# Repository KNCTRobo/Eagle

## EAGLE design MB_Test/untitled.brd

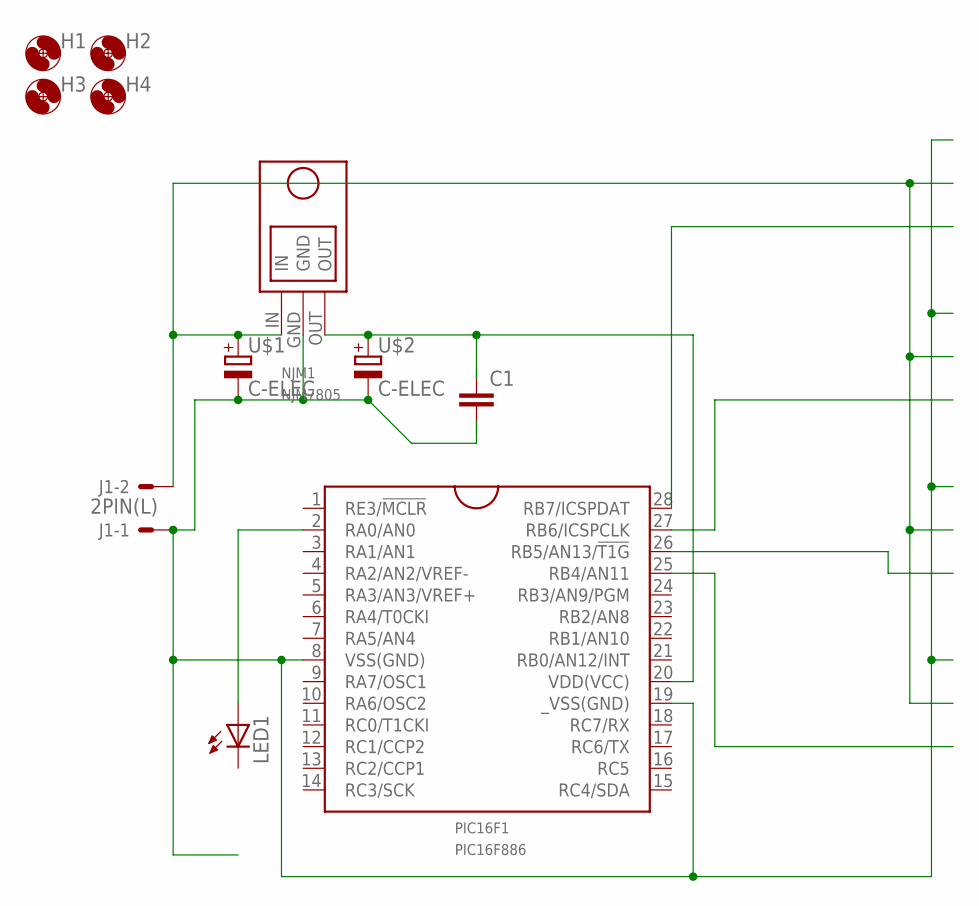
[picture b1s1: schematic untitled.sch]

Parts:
C1: C-; C-2.54
H1, H2, H3, H4: HOLE3.3M3BOLT; HOLE3.3
J1: 2PIN(L); 2PL
LED1: LED; LED5MM
NJM1: NJM7805
PIC16F1: PIC16F886; DIL28-3
U$1, U$2: C-ELEC; C-6MM

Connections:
unnamed: J1.1, NJM1.GND, PIC16F1.8 (VSS(GND)), PIC16F1.19 (_VSS(GND)), U$1.-, U$2.-
unnamed: J1.2, NJM1.IN, U$1.+
unnamed: NJM1.OUT, PIC16F1.20 (VDD(VCC)), U$2.+
unnamed: LED1.A, PIC16F1.2 (RA0/AN0)

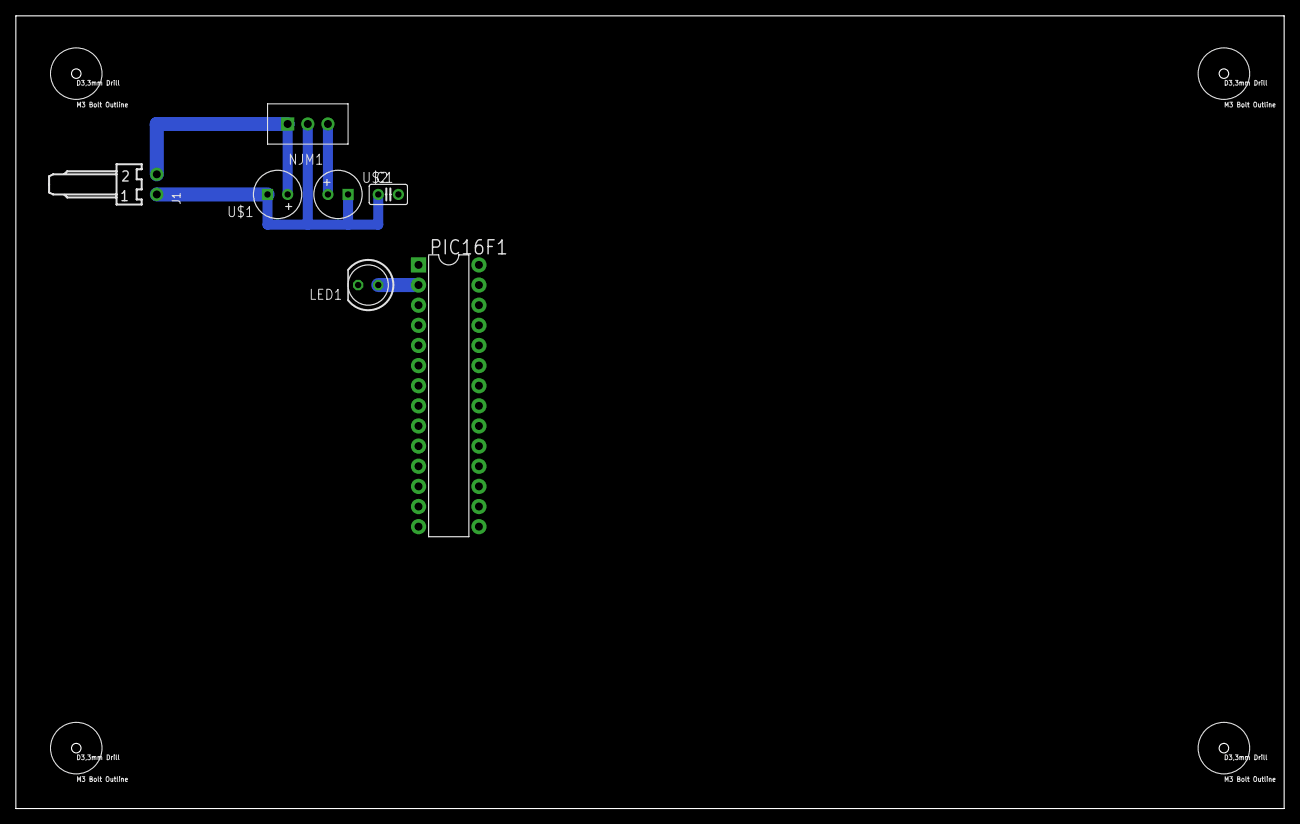
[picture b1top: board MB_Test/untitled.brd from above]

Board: 2 copper layers, 160.0 x 100.0 mm, 11 parts (0 on the bottom side), 4 nets.

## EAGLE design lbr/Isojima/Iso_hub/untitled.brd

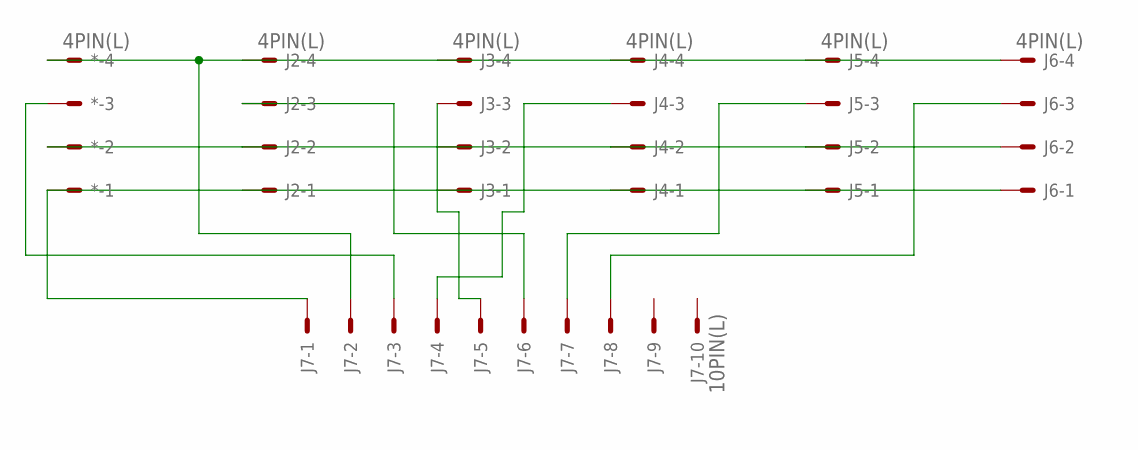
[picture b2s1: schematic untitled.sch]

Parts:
*: 4PIN(L); 4PL
J2, J3, J4, J5, J6: 4PIN(L); 4PL
J7: 10PIN(L); 10PL

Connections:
unnamed: *.4, J2.4, J3.4, J4.4, J5.4, J6.4, J7.2
unnamed: *.1, J2.1, J3.1, J4.1, J5.1, J6.1, J7.1
unnamed: *.2, J2.2, J3.2, J4.2, J5.2, J6.2
unnamed: *.3, J7.3
unnamed: J2.3, J7.6
unnamed: J3.3, J7.5
unnamed: J4.3, J7.4
unnamed: J5.3, J7.7
unnamed: J6.3, J7.8

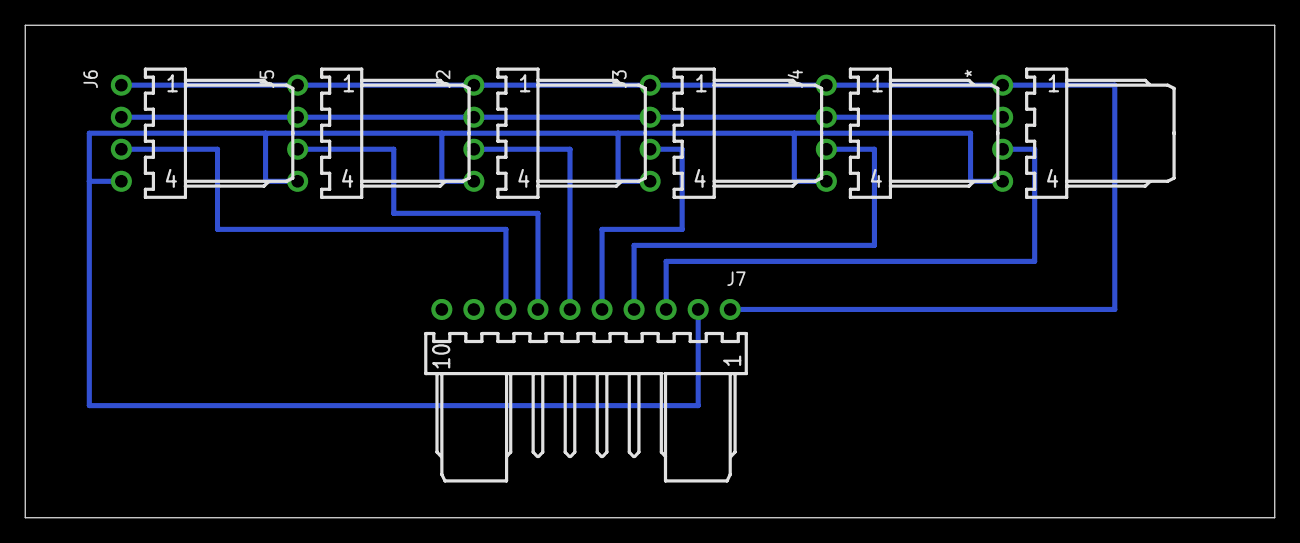
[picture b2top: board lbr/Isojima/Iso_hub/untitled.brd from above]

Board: 2 copper layers, 99.0 x 39.0 mm, 7 parts (0 on the bottom side), 9 nets.

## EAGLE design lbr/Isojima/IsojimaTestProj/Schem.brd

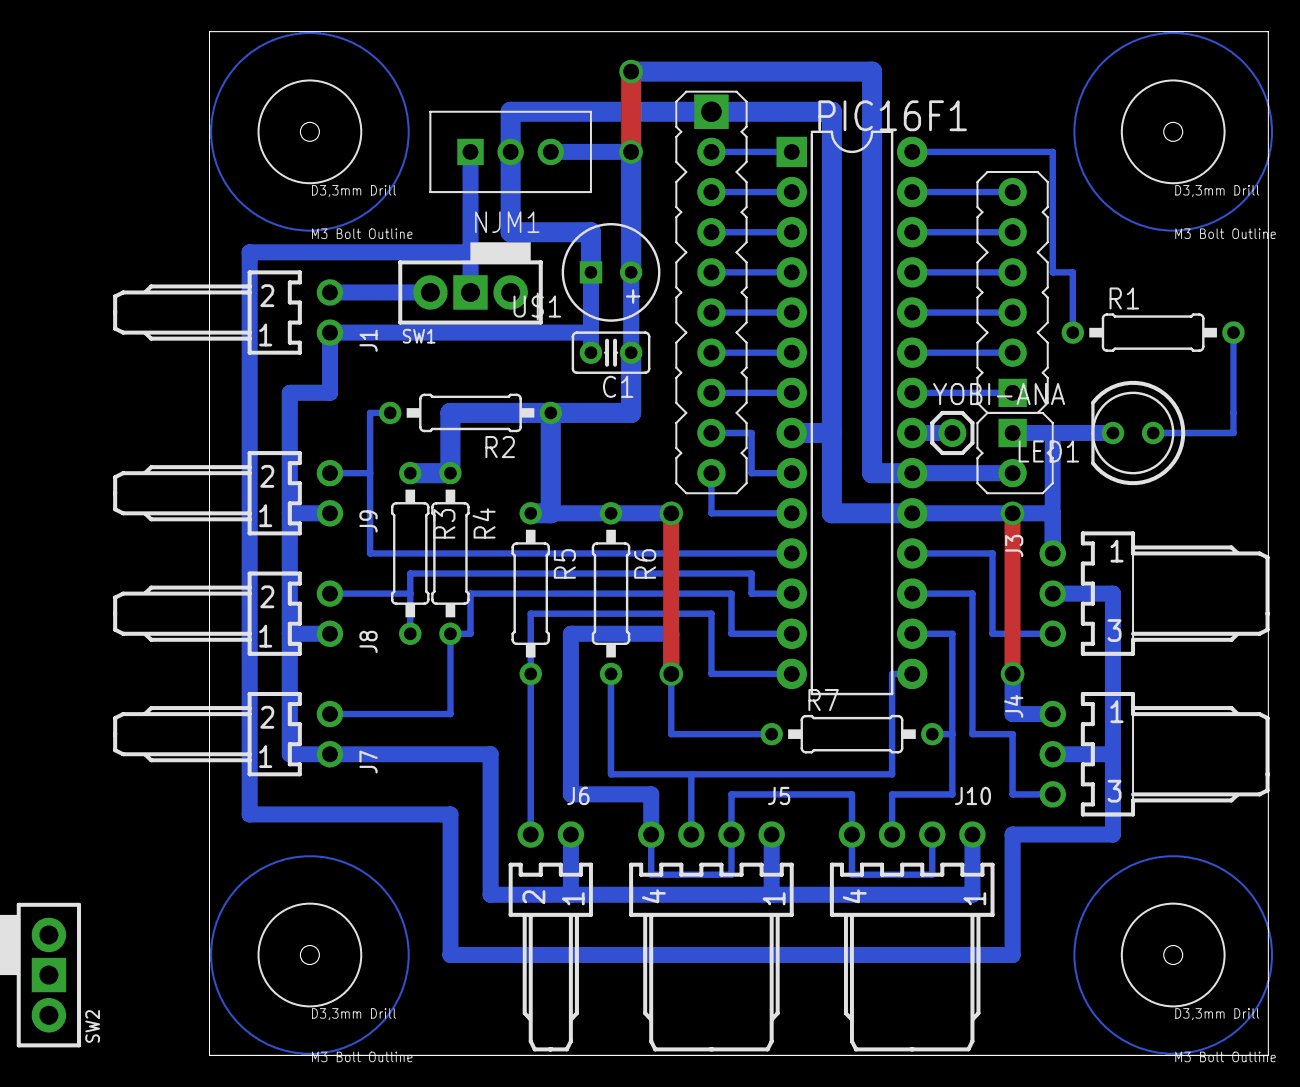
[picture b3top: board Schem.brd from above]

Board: 2 copper layers, 67.0 x 64.8 mm, 31 parts (0 on the bottom side), 30 nets.

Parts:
C1: C-2.54
H1, H2, H3, H4: HOLE3.3M3BOLT; HOLE3.3
J1, J6, J7, J8, J9: 2PIN(L); 2PL
J2: PINHD1X2
J3, J4: 3PIN(L); 3PL
J5, J10: 4PIN(L); 4PL
JT1: PINHD1X6
JT2: PINHD1X10
LED1: LED5MM
NJM1: NJM7805
PIC16F1: PIC16F886; DIL28-3
R1, R2, R3, R4, R5, R6, R7: 0207/10
SW1, SW2: SWITCH_MINI
U$1: C-ELEC; C-6MM
YOBI-ANA: 1X01_SMALL

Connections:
+5V: C1.P$1, J2.P$2, J5.2, J5.4, J10.2, J10.4, NJM1.OUT, PIC16F1.20, R2.1, R3.1, R4.1, R5.1, R6.1, R7.1, U$1.+
+12V: J3.2, J4.2, NJM1.IN, SW1.COM
GND: C1.P$2, J1.1, J2.P$1, J3.1, J4.1, J5.1, J6.1, J7.1, J8.1, J9.1, J10.1, JT2.0, LED1.K, NJM1.GND, PIC16F1.8, PIC16F1.19, U$1.-
unnamed: JT1.9, PIC16F1.27
unnamed: JT1.8, PIC16F1.26
unnamed: JT1.3, PIC16F1.25
unnamed: JT1.2, PIC16F1.24
unnamed: JT1.1, PIC16F1.23
unnamed: PIC16F1.28, R1.1
unnamed: LED1.A, R1.2
unnamed: JT1.0, PIC16F1.22
unnamed: J4.3, PIC16F1.17
unnamed: J3.3, PIC16F1.18
unnamed: J9.2, PIC16F1.11, R2.2
unnamed: J1.2, SW1.2
unnamed: J7.2, PIC16F1.13, R4.2
unnamed: J6.2, PIC16F1.14, R5.2
unnamed: J8.2, PIC16F1.12, R3.2
unnamed: J5.3, PIC16F1.15, R6.2
unnamed: PIC16F1.21, YOBI-ANA.1
unnamed: JT2.9, PIC16F1.10
unnamed: JT2.8, PIC16F1.9
unnamed: JT2.7, PIC16F1.7
unnamed: JT2.6, PIC16F1.6
unnamed: JT2.5, PIC16F1.5
unnamed: JT2.4, PIC16F1.4
unnamed: JT2.3, PIC16F1.3
unnamed: JT2.2, PIC16F1.2
unnamed: JT2.1, PIC16F1.1
unnamed: J10.3, PIC16F1.16, R7.2

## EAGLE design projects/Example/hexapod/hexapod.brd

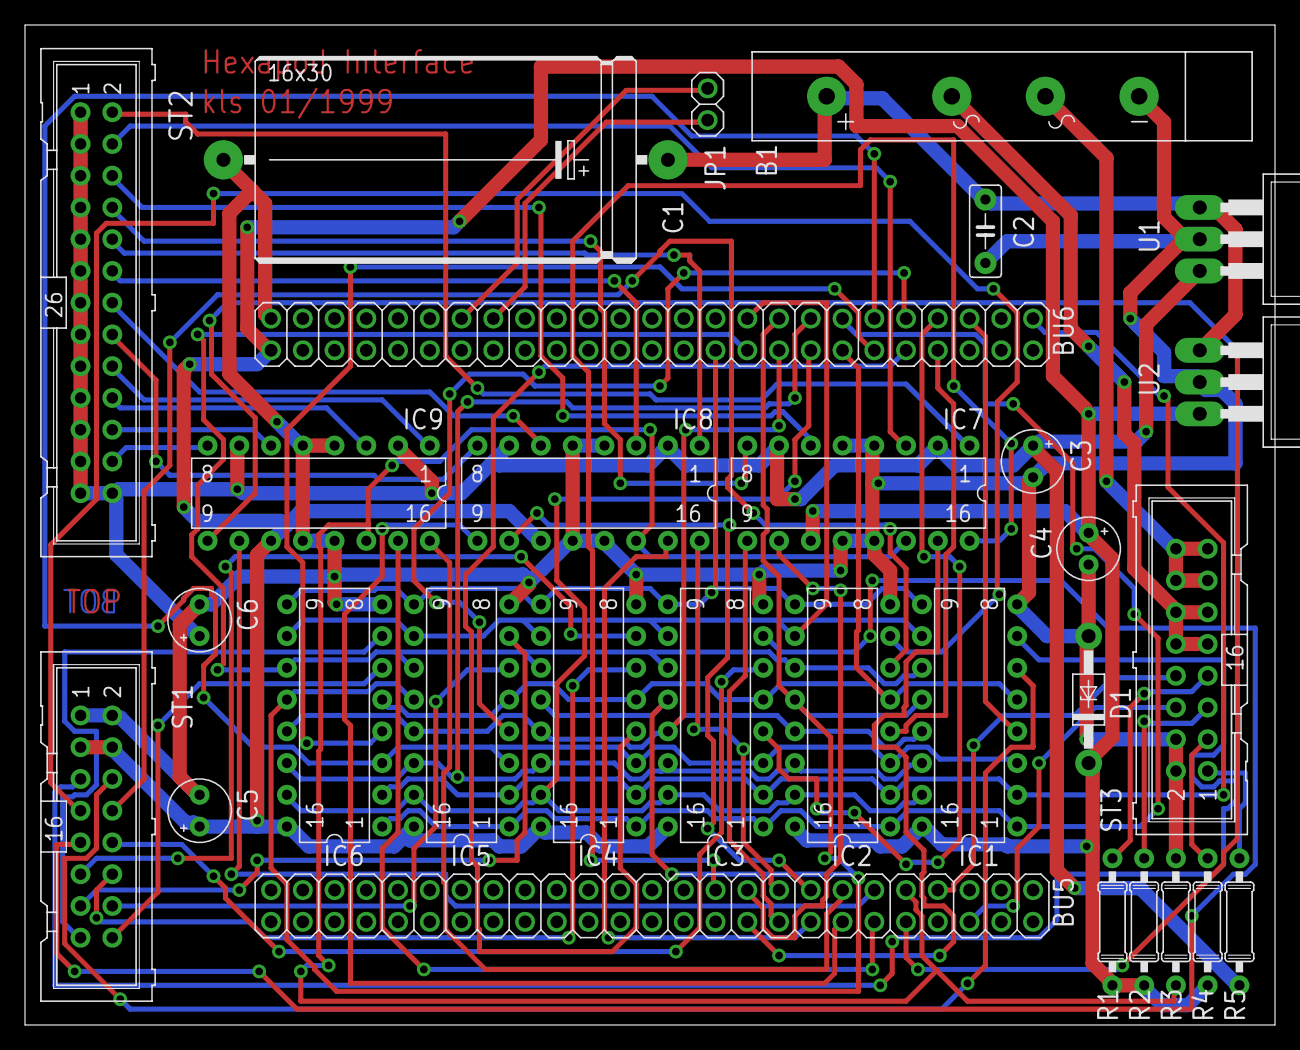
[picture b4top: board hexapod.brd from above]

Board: 2 copper layers, 100.0 x 80.0 mm, 30 parts (0 on the bottom side), 68 nets.

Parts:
B1: FB100
BU5, BU6: PINHD-2X25; 2X25
C1: 2200uF/35V; E35-16
C2: 100nf; C5B2,5A
C3, C6: 4,7uf/35V; E2,5-5
C4, C5: 4,7uf/10V; E2,5-5
D1: BZX85; DO41Z10
IC1, IC2, IC3, IC4, IC5, IC6: HCTL2016; DIL-16
IC7, IC8, IC9: DS3668; DIL-16
JP1: PINHD-1X2; 1X02
R1, R2, R4, R5: 0207/10
R3: 10k; 0207/10@1
ST1, ST3: PINHD-2X8; ML16
ST2: PINHD-2X13; ML26
U1: 78S24; TO220H
U2: 7805; TO220H

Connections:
!OE0: BU6.5, IC1.4
!OE1: BU6.8, IC2.4
!OE2: BU6.7, IC3.4
!OE3: BU6.10, IC4.4
!OE4: BU6.9, IC5.4
!OE5: BU6.12, IC6.4
!RST: BU6.14, IC1.5, IC2.5, IC3.5, IC4.5, IC5.5, IC6.5
+5V: BU6.50, C4.+, C5.+, D1.K, IC1.16, IC2.16, IC3.16, IC4.16, IC5.16, IC6.16, IC7.11, IC8.11, IC9.11, R1.1, R2.1, R4.1, ST1.3, ST1.4, U2.3
+24V: C3.+, C6.+, IC7.2, IC7.7, IC8.2, IC8.7, IC9.2, IC9.7, R5.1, ST2.1, ST2.3, ST2.5, ST2.7, ST2.9, ST2.11, ST2.13, ST2.15, ST2.17, ST2.19, ST2.21, ST2.23, ST2.25, ST2.26, U1.3
AC1: B1.AC1, ST3.9, ST3.10, ST3.11, ST3.12
AC2: B1.AC2, ST3.13, ST3.14, ST3.15, ST3.16
CLK: BU6.1, IC1.2, IC2.2, IC3.2, IC4.2, IC5.2, IC6.2
COIL0: IC7.1, ST2.2
COIL1: IC7.3, ST2.4
COIL2: IC7.6, ST2.6
COIL3: IC7.8, ST2.8
COIL4: IC8.1, ST2.10
COIL5: IC8.3, ST2.12
COIL6: IC8.6, ST2.14
COIL7: IC8.8, ST2.16
COIL8: IC9.1, ST2.18
COIL9: IC9.3, ST2.20
COIL10: IC9.6, ST2.22
COIL11: IC9.8, ST2.24
D0: BU6.13, IC1.1, IC2.1, IC3.1, IC4.1, IC5.1, IC6.1
D1: BU6.16, IC1.15, IC2.15, IC3.15, IC4.15, IC5.15, IC6.15
D2: BU6.15, IC1.14, IC2.14, IC3.14, IC4.14, IC5.14, IC6.14
D3: BU6.18, IC1.13, IC2.13, IC3.13, IC4.13, IC5.13, IC6.13
D4: BU6.17, IC1.12, IC2.12, IC3.12, IC4.12, IC5.12, IC6.12
D5: BU6.20, IC1.11, IC2.11, IC3.11, IC4.11, IC5.11, IC6.11
D6: BU6.19, IC1.10, IC2.10, IC3.10, IC4.10, IC5.10, IC6.10
D7: BU6.22, IC1.9, IC2.9, IC3.9, IC4.9, IC5.9, IC6.9
EN: BU5.9, IC7.14, IC8.14, IC9.14, R3.2
ENC0: IC1.7, ST1.5
ENC1: IC1.6, ST1.6
ENC2: IC2.7, ST1.7
ENC3: IC2.6, ST1.8
ENC4: IC3.7, ST1.9
ENC5: IC3.6, ST1.10
ENC6: IC4.7, ST1.11
ENC7: IC4.6, ST1.12
ENC8: IC5.7, ST1.13
ENC9: IC5.6, ST1.14
ENC10: IC6.7, ST1.15
ENC11: IC6.6, ST1.16
GND: B1.-, BU6.49, C1.-, C2.1, C3.-, C4.-, C5.-, C6.-, D1.A, IC1.8, IC2.8, IC3.8, IC4.8, IC5.8, IC6.8, IC7.4, IC7.5, IC7.12, IC7.13, IC8.4, IC8.5, IC8.12, IC8.13, IC9.4, IC9.5, IC9.12, IC9.13, R3.1, ST1.1, ST1.2, ST3.2, ST3.4, U1.2, U2.2
unnamed: R5.2, ST3.1
unnamed: R4.2, ST3.3
unnamed: R2.2, ST3.5
unnamed: R1.2, ST3.7
unnamed: BU6.35, JP1.2
unnamed: BU6.37, JP1.1
SEL: BU6.11, IC1.3, IC2.3, IC3.3, IC4.3, IC5.3, IC6.3
STATUS0: BU5.7, ST3.8
STATUS1: BU5.6, ST3.6
VALVE0: BU5.21, IC7.16
VALVE1: BU5.20, IC7.15
VALVE2: BU5.19, IC7.10
VALVE3: BU5.18, IC7.9
VALVE4: BU5.17, IC8.16
VALVE5: BU5.16, IC8.15
VALVE6: BU5.15, IC8.10
VALVE7: BU5.14, IC8.9
VALVE8: BU5.13, IC9.16
VALVE9: BU5.12, IC9.15
VALVE10: BU5.11, IC9.10
VALVE11: BU5.10, IC9.9
VIN: B1.+, C1.+, C2.2, U1.1, U2.1

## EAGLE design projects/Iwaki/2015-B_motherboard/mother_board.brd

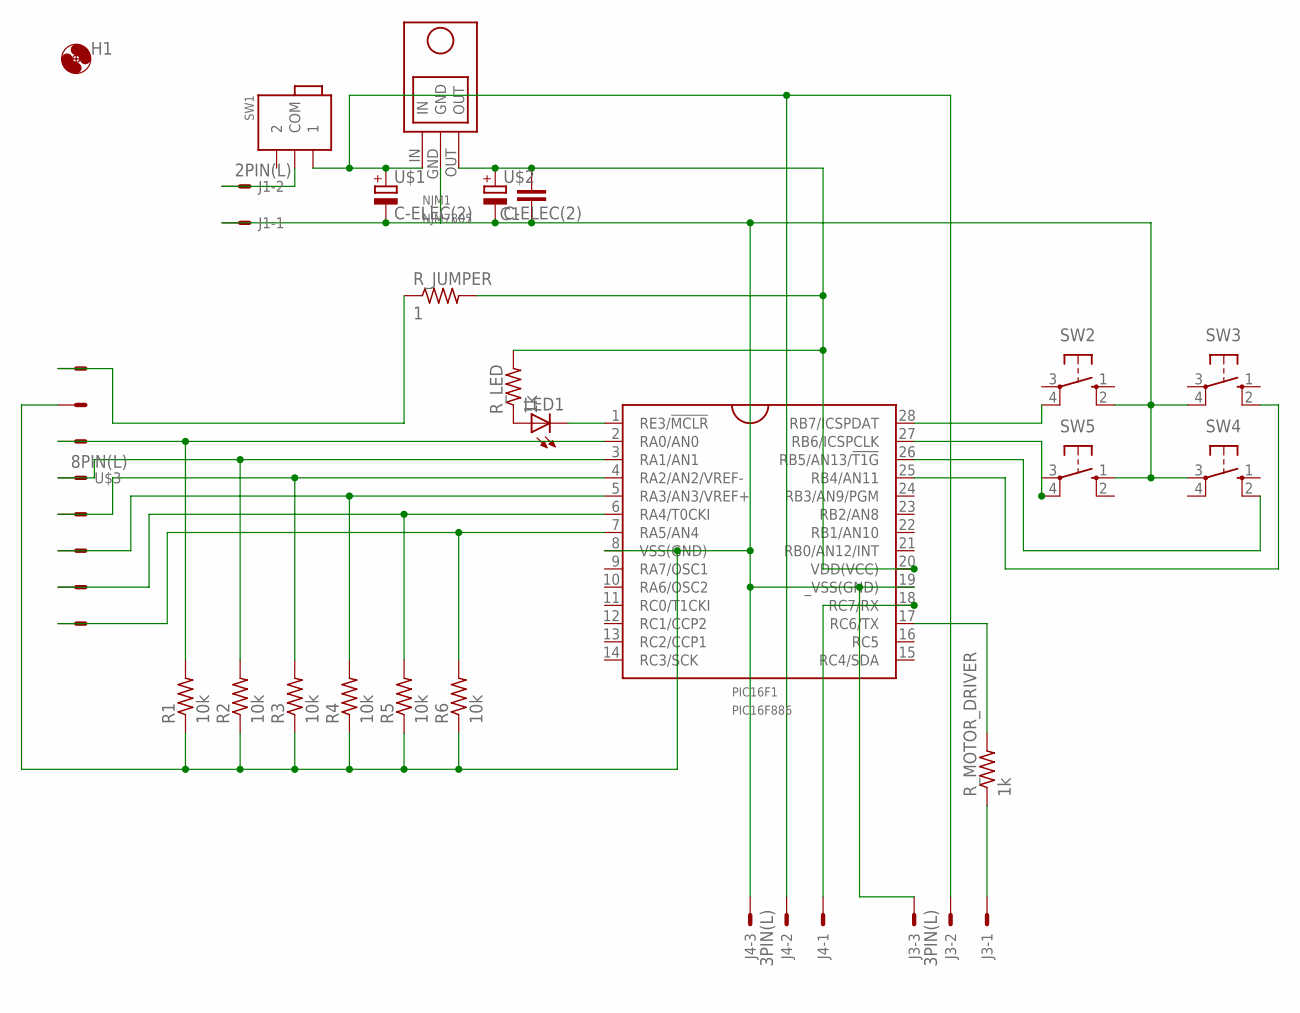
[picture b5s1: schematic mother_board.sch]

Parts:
C1: C-3
H1: HOLE3.3M3BOLT; HOLE3.3
J1: 2PIN(L); 2PL
J3, J4: 3PIN(L); 3PL
LED1: LED-2; LED5MM-2
NJM1: NJM7805
PIC16F1: PIC16F886; DIL28-3
R1, R2, R3, R4, R5, R6: 10k; 0207/10
R_JUMPER: 1; 0207/10
R_LED: 1k; 0207/10
R_MOTOR_DRIVER: 1k; 0207/10
SW1: SWITCH_MININORMAL; SWITCH_MINI
SW2, SW3, SW4, SW5: TACTSW; TACT
U$1, U$2: C-ELEC(2); C-6MM(2)
U$3: 8PIN(L); 8PL

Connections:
5V: C1.2, NJM1.OUT, PIC16F1.20 (VDD(VCC)), R_JUMPER.2, R_LED.2, U$2.+
9V: J1.2, J3.2, J4.2, NJM1.IN, SW1.1, SW1.COM, U$1.+
A0: PIC16F1.2 (RA0/AN0), R1.2, U$3.P6
A1: PIC16F1.3 (RA1/AN1), R2.2, U$3.P5
A2: PIC16F1.4 (RA2/AN2/VREF-), R3.2, U$3.P4
A3: PIC16F1.5 (RA3/AN3/VREF+), R4.2, U$3.P3
A4: PIC16F1.6 (RA4/T0CKI), R5.2, U$3.P2
A5: PIC16F1.7 (RA5/AN4), R6.2, U$3.P1
B4: PIC16F1.25 (RB4/AN11), SW3.2 (S1)
B5: PIC16F1.26 (RB5/AN13/!T1G), SW4.2 (S1)
B6: PIC16F1.27 (RB6/ICSPCLK), SW5.4 (P1)
B7: PIC16F1.28 (RB7/ICSPDAT), SW2.4 (P1)
GND1: C1.1, J1.1, J3.3, J4.3, NJM1.GND, PIC16F1.8 (VSS(GND)), PIC16F1.19 (_VSS(GND)), R1.1, R2.1, R3.1, R4.1, R5.1, R6.1, SW2.2 (S1), SW3.4 (P1), SW4.3, SW5.1 (S), U$1.-, U$2.-, U$3.P7
unnamed: LED1.K (C), PIC16F1.1 (RE3/!MCLR)
unnamed: R_JUMPER.1, U$3.P8
unnamed: PIC16F1.17 (RC6/TX), R_MOTOR_DRIVER.2
unnamed: LED1.A, R_LED.1
SIGNAL_MOTOR_DORIVER: J3.1, R_MOTOR_DRIVER.1
SIGNAL_XBEE: J4.1, PIC16F1.18 (RC7/RX)

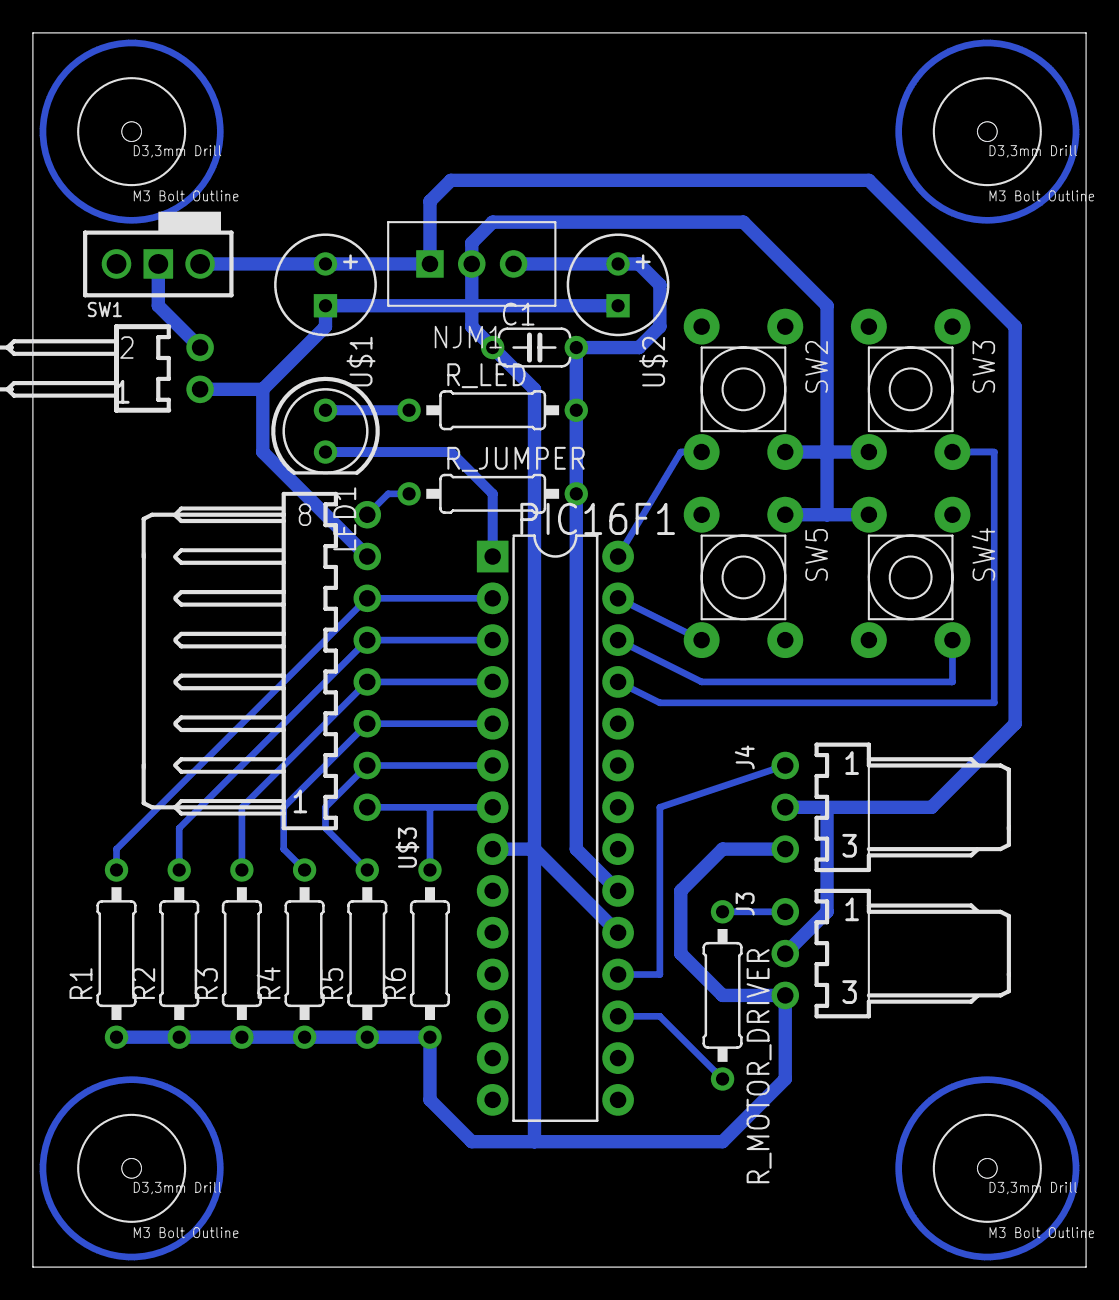
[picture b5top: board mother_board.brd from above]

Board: 2 copper layers, 64.0 x 75.0 mm, 28 parts (0 on the bottom side), 19 nets.

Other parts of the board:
H2, H3, H4: HOLE3.3M3BOLT; HOLE3.3

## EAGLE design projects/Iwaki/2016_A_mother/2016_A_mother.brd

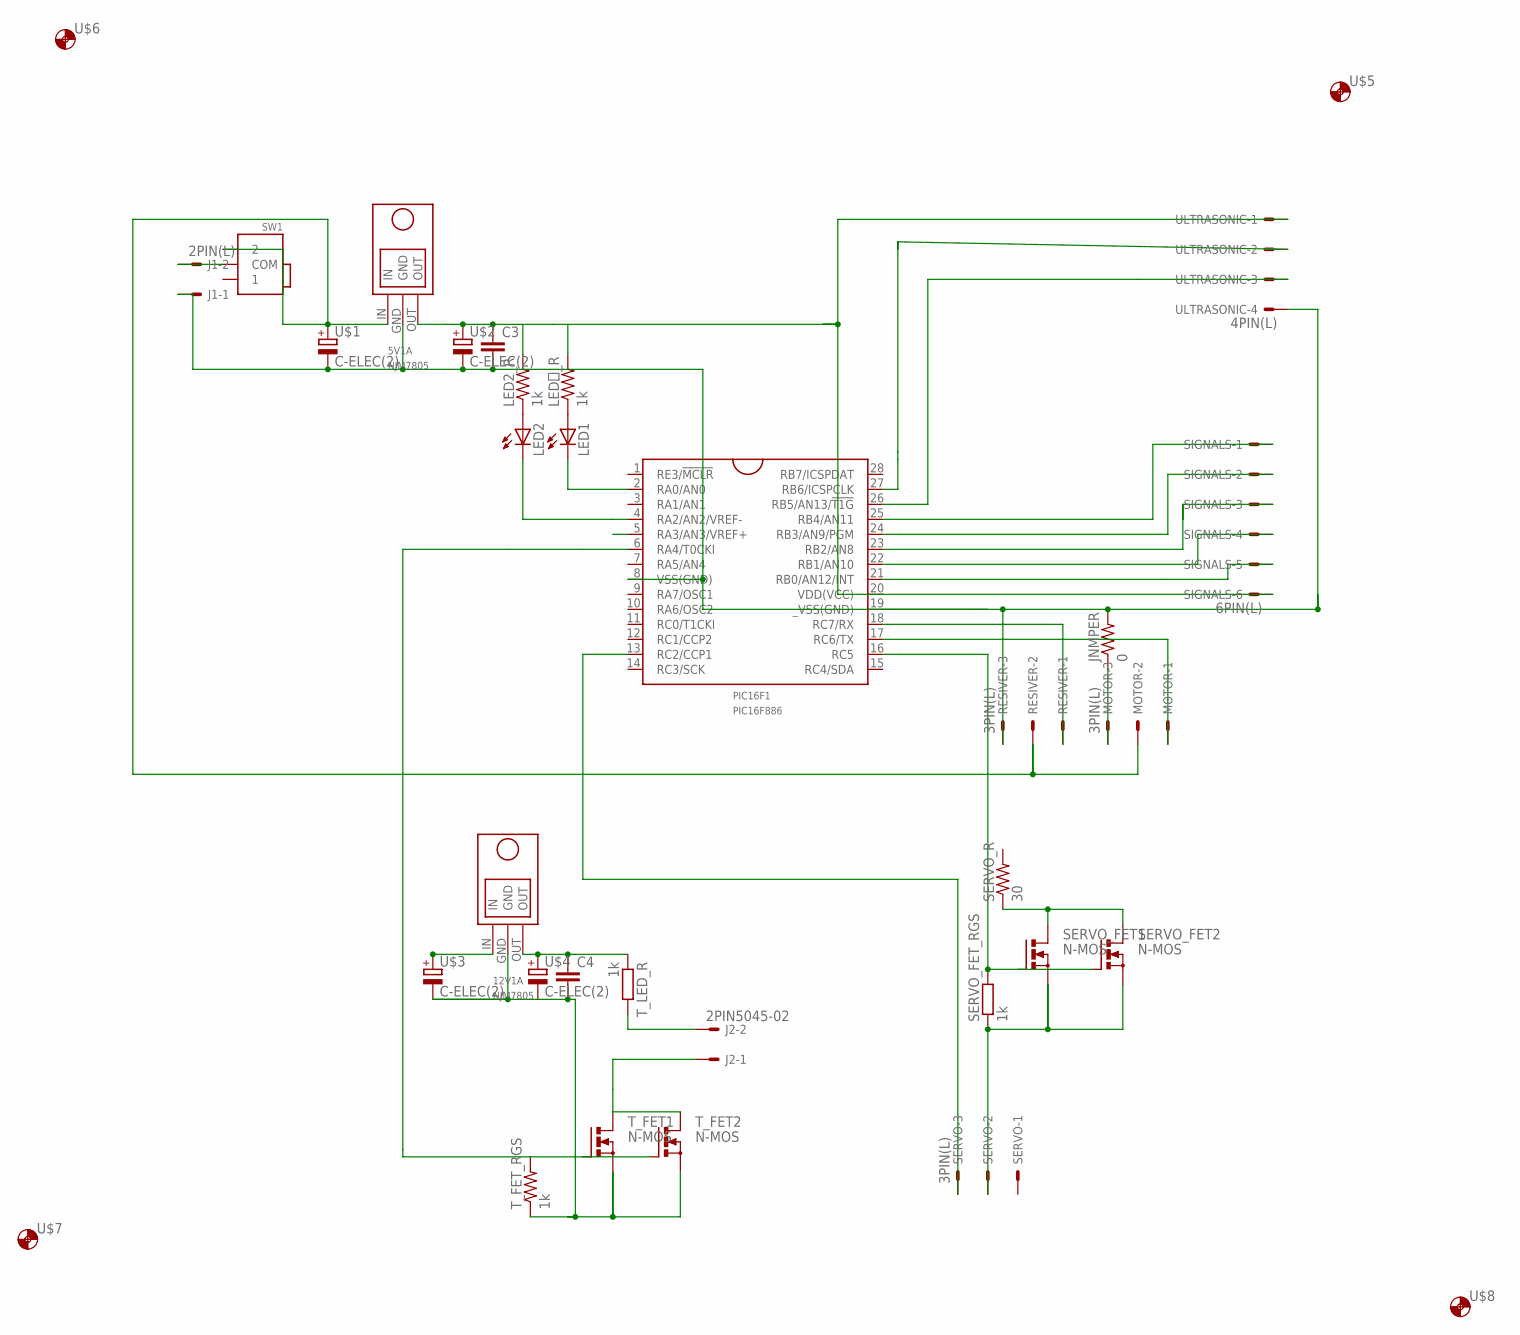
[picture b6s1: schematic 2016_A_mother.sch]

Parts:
5V1A, 12V1A: NJM7805
C3, C4: C-; C-2.54
J1: 2PIN(L); 2PL
J2: 2PIN5045-02; 5045-02
JNMPER: 0; 0207/10
LED1: LED; LED5MM
LED2: LED-2; LED5MM-2
LED2_R, LED１_R: 1k; 0207/10
MOTOR: 3PIN(L); 3PL
PIC16F1: PIC16F886; DIL28-3
RESIVER: 3PIN(L); 3PL
SERVO: 3PIN(L); 3PL
SERVO_FET1, SERVO_FET2: N-MOS; TO220BV
SERVO_FET_RGS: 1k; R0207V
SERVO_R: 30; 0207/10
SIGNALS: 6PIN(L); 6PL
SW1: SWITCH_MININORMAL; SWITCH_MINI
T_FET1, T_FET2: N-MOS; TO220BV
T_FET_RGS: 1k; 0207/10
T_LED_R: 1k; R0207V
U$1, U$2, U$3, U$4: C-ELEC(2); C-6MM(2)
U$5, U$6, U$7, U$8: 1MMDRILL; 1MDRILL
ULTRASONIC: 4PIN(L); 4PL

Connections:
5V: 5V1A.OUT, C3.P$1 (1), LED2_R.2, LED１_R.2, PIC16F1.20 (VDD(VCC)), SIGNALS.6, U$2.+, ULTRASONIC.1
9V: 5V1A.IN, MOTOR.2, RESIVER.2, SW1.2, U$1.+
12V: 12V1A.OUT, C4.P$1 (1), T_LED_R.1, U$4.+
G: PIC16F1.16 (RC5), SERVO_FET1.G, SERVO_FET2.G, SERVO_FET_RGS.2
GND: 5V1A.GND, C3.P$2 (2), J1.1, JNMPER.2, PIC16F1.8 (VSS(GND)), PIC16F1.19 (_VSS(GND)), RESIVER.3, U$1.-, U$2.-, ULTRASONIC.4
LI-FE: 12V1A.IN, U$3.+
MOTOR_SIGNAL: MOTOR.1, PIC16F1.17 (RC6/TX)
unnamed: J1.2, SW1.COM
unnamed: PIC16F1.21 (RB0/AN12/INT), SIGNALS.5
unnamed: PIC16F1.22 (RB1/AN10), SIGNALS.4
unnamed: PIC16F1.23 (RB2/AN8), SIGNALS.3
unnamed: PIC16F1.24 (RB3/AN9/PGM), SIGNALS.2
unnamed: PIC16F1.25 (RB4/AN11), SIGNALS.1
unnamed: LED1.A, LED１_R.1
unnamed: LED1.K (C), PIC16F1.2 (RA0/AN0)
unnamed: J2.P$1, T_LED_R.2
unnamed: J2.P$2, T_FET1.D, T_FET2.D
unnamed: JNMPER.1, MOTOR.3
unnamed: PIC16F1.26 (RB5/AN13/!T1G), ULTRASONIC.3
unnamed: PIC16F1.27 (RB6/ICSPCLK), ULTRASONIC.2
unnamed: LED2.K (C), PIC16F1.4 (RA2/AN2/VREF-)
unnamed: LED2.A, LED2_R.1
unnamed: SERVO_FET1.D, SERVO_FET2.D, SERVO_R.1
unnamed: PIC16F1.13 (RC2/CCP1), SERVO.3
unnamed: SERVO.2, SERVO_FET1.S, SERVO_FET2.S, SERVO_FET_RGS.1
T_GND: 12V1A.GND, C4.P$2 (2), T_FET1.S, T_FET2.S, T_FET_RGS.1, U$3.-, U$4.-
T_VGS: PIC16F1.6 (RA4/T0CKI), T_FET1.G, T_FET2.G, T_FET_RGS.2
XBEE_SIGNAL: PIC16F1.18 (RC7/RX), RESIVER.1

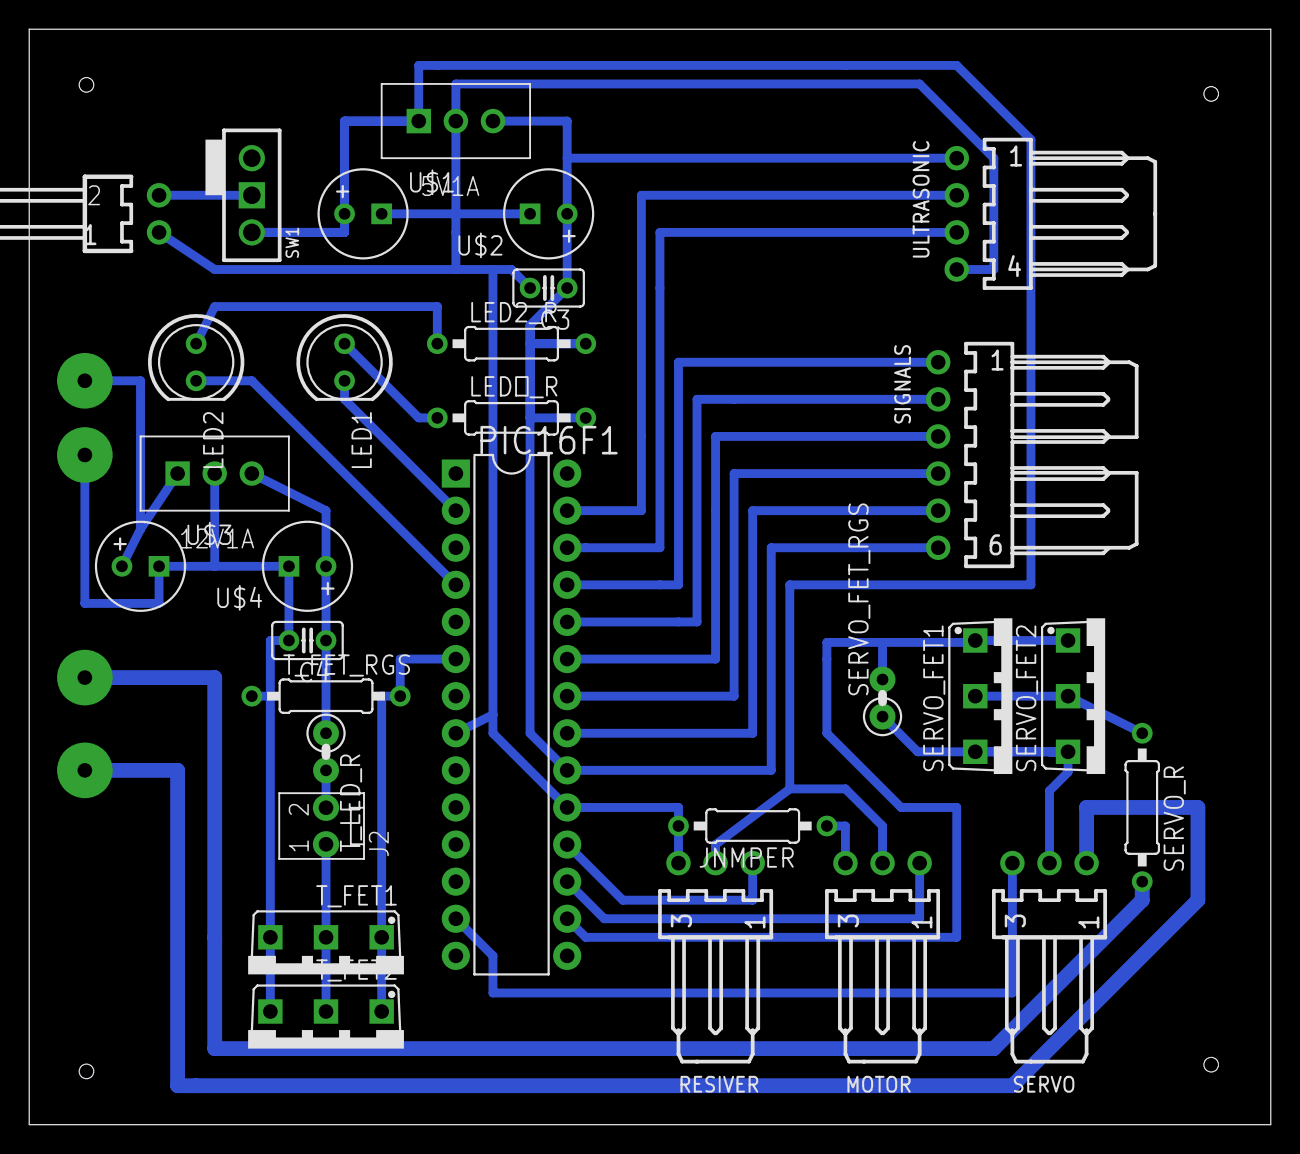
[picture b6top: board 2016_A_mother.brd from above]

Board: 2 copper layers, 85.0 x 75.0 mm, 34 parts (0 on the bottom side), 28 nets.

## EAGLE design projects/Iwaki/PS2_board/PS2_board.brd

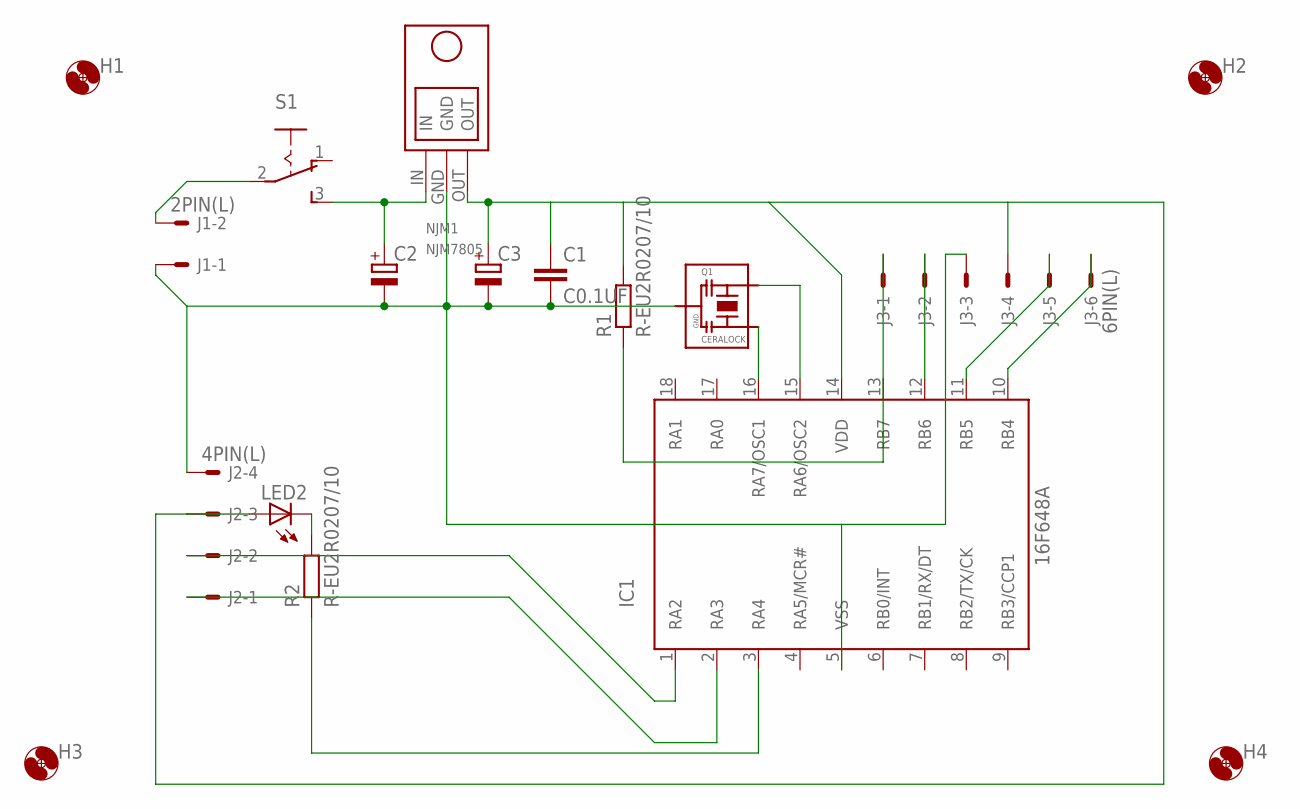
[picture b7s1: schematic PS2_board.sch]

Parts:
C1: C0.1UF
C2, C3: CPOL-EU2-5MM; E2-5
H1, H2, H3, H4: HOLE3.3M3BOLT; HOLE3.3
IC1: 16F648A; 18PIN
J1: 2PIN(L); 2PL
J2: 4PIN(L); 4PL
J3: 6PIN(L); 6PL
LED2: LED5MM
NJM1: NJM7805
Q1: CERALOCK
R1, R2: R-EU2R0207/10; 0207/10
S1: SLIDESW

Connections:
unnamed: J1.2, S1.2
unnamed: C2.+, NJM1.IN, S1.3
unnamed: C1.1, C3.+, IC1.14 (VDD), J2.3, J3.4, LED2.A, NJM1.OUT, R1.2
unnamed: IC1.16 (RA7/OSC1), Q1.P$3
unnamed: IC1.15 (RA6/OSC2), Q1.P$1
unnamed: IC1.11 (RB5), J3.5
unnamed: IC1.12 (RB6), J3.2
unnamed: IC1.10 (RB4), J3.6
unnamed: IC1.13 (RB7), J3.1, R1.1
unnamed: C1.2, C2.-, C3.-, IC1.5 (VSS), J1.1, J2.4, J3.3, NJM1.GND, Q1.P$2
unnamed: IC1.2 (RA3), J2.1
unnamed: IC1.1 (RA2), J2.2
unnamed: IC1.3 (RA4), R2.1
unnamed: LED2.K (C), R2.2

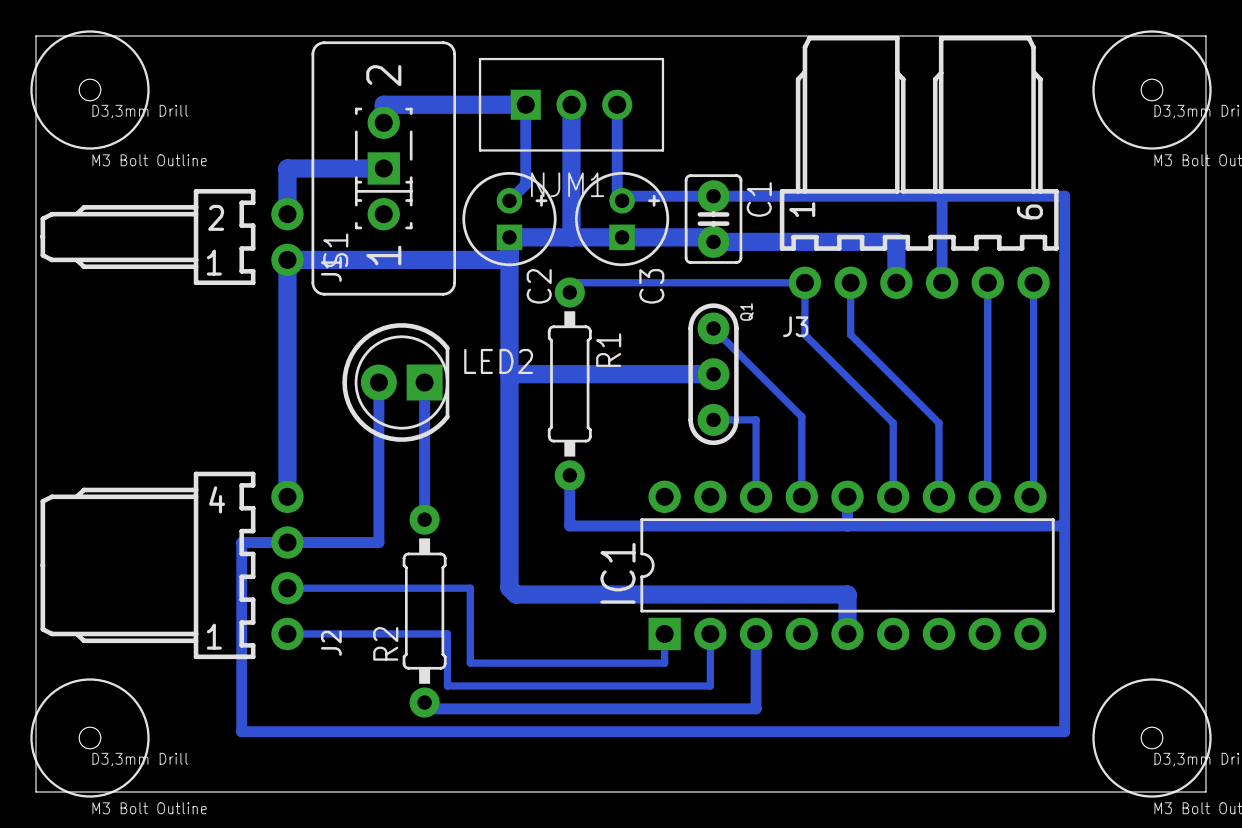
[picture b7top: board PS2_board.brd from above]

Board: 2 copper layers, 65.0 x 42.0 mm, 17 parts (0 on the bottom side), 14 nets.

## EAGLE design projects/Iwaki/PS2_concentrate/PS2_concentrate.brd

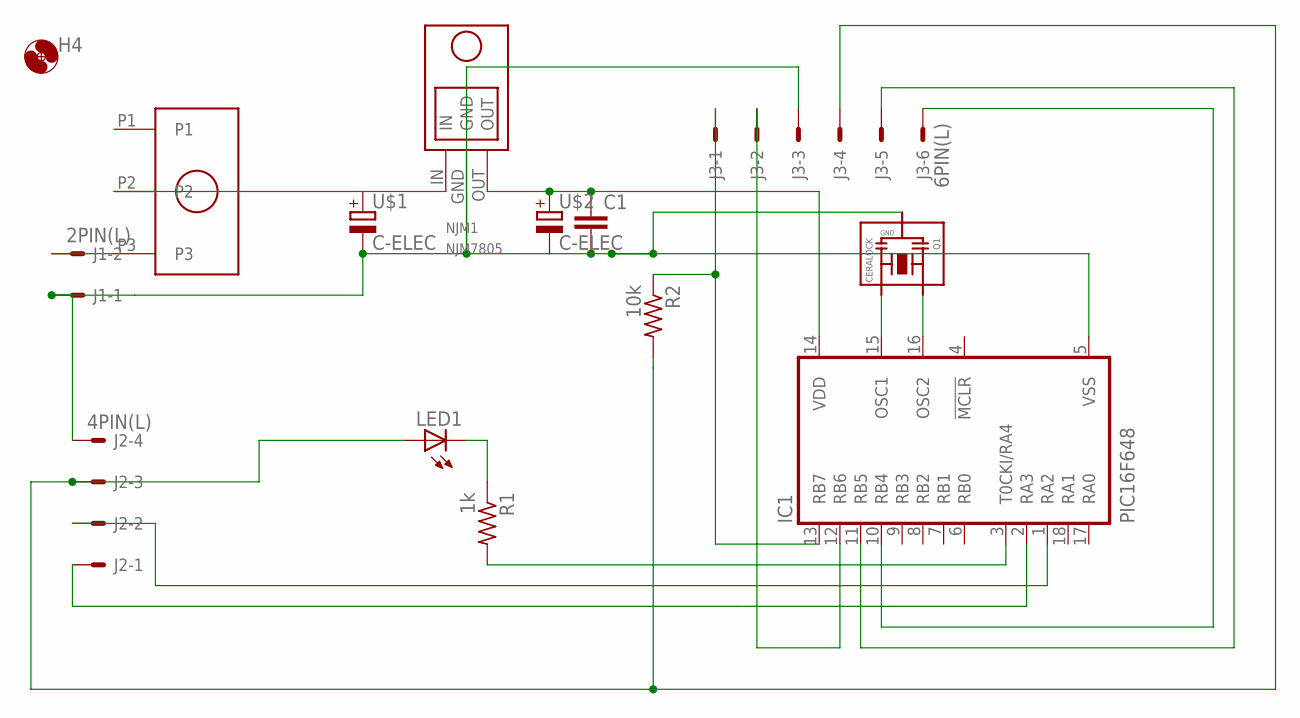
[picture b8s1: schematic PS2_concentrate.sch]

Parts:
C1: C-; C-2.54
H4: HOLE3.3M3BOLT; HOLE3.3
IC1: PIC16F648; DIL18
J1: 2PIN(L); 2PL
J2: 4PIN(L); 4PL
J3: 6PIN(L); 6PL
LED1: LED; LED5MM
NJM1: NJM7805
Q1: CERALOCK
R1: 1k; 0207/10
R2: 10k; 0207/10
U$1, U$2: C-ELEC; C-6MM
U$3: TOGGLE_SEITCH; TOGGLE_SWITCH

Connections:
5V: C1.P$1 (1), IC1.14 (VDD), J2.3, J3.4, LED1.A, NJM1.OUT, R2.2, U$2.+
9V: NJM1.IN, U$1.+, U$3.P2
A2: IC1.1 (RA2), J2.2
A3: IC1.2 (RA3), J2.1
A4: IC1.3 (T0CKI/RA4), R1.2
B4: IC1.10 (RB4), J3.6
B5: IC1.11 (RB5), J3.5
B6: IC1.12 (RB6), J3.2
B7: IC1.13 (RB7), J3.1, R2.1
GND: C1.P$2 (2), IC1.5 (VSS), J1.1, J2.4, J3.3, NJM1.GND, Q1.P$2, U$1.-, U$2.-
unnamed: LED1.K (C), R1.1
unnamed: J1.2, U$3.P3
unnamed: IC1.15 (OSC1), Q1.P$3
unnamed: IC1.16 (OSC2), Q1.P$1

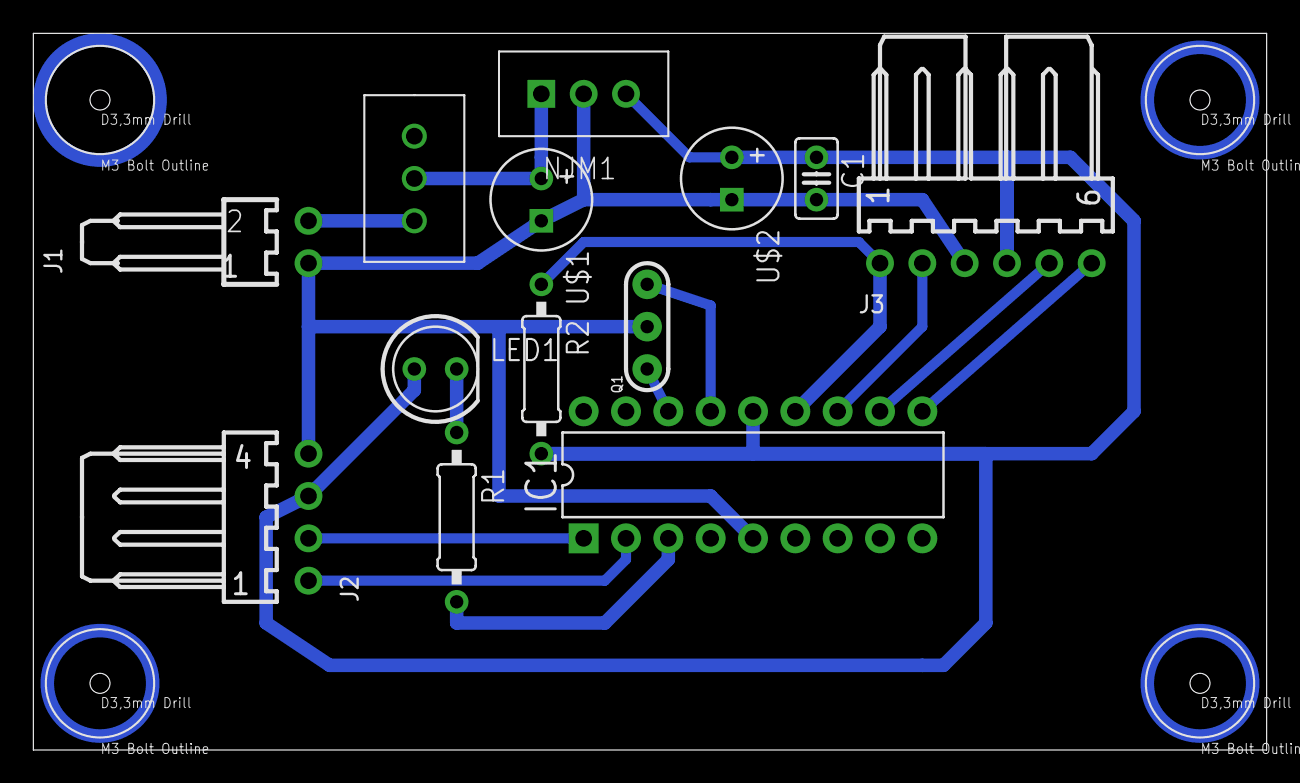
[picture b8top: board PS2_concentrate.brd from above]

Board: 2 copper layers, 74.0 x 43.0 mm, 17 parts (0 on the bottom side), 14 nets.

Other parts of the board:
H1, H2, H3: HOLE3.3M3BOLT; HOLE3.3
